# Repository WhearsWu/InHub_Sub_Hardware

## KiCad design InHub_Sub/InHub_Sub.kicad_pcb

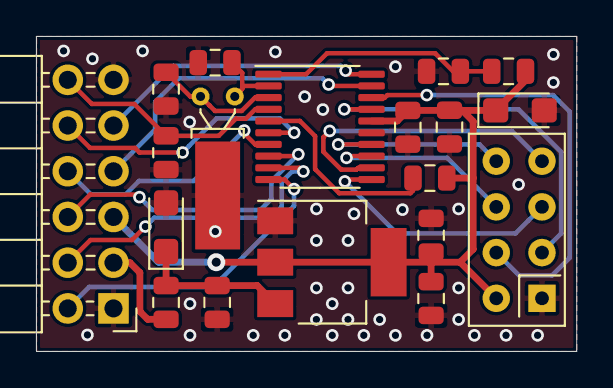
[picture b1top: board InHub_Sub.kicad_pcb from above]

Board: 2 copper layers, 30.0 x 17.5 mm, 19 parts (0 on the bottom side), 22 nets.

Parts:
C1: 0.1uF; C_0805_2012Metric
C2: 10uF_T; CP_EIA-3216-12_Kemet-S
C3: 22uF_T; CP_EIA-3216-12_Kemet-S
C4, C5: 10pF; C_0805_2012Metric
C6: 1uF; C_0805_2012Metric
C7, C10: 100nF; C_0805_2012Metric
C8: 10nF; C_0805_2012Metric
C9: 10uF; C_0805_2012Metric
F1: Fuse_Small; Fuse_0805_2012Metric
FB1: Ferrite_Bead_Small; L_0805_2012Metric
J2: Conn_02x06_Odd_Even; PinHeader_2x06_P2.54mm_Horizontal
R1, R2: 1kO; R_0805_2012Metric
U1: AMS1117-3.3; SOT-223-3_TabPin2
U2: STM32L011F4Px; TSSOP-20_4.4x6.5mm_P0.65mm
U3: NRF24L01_Breakout; nRF24L01_Breakout
Y1: 32.768kHz; Crystal_DS26_D2.0mm_L6.0mm_Horizontal_1EP_style1

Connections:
+3.3VA: FB1.2, U2.5
+3V3: C3.1, C6.1, C7.1, C9.1, C10.1, FB1.1, J2.5, R1.2, U1.2, U2.16, U3.2
+5V: F1.1, J2.3
/BOOT0: R1.1, R2.2, U2.1
/NRST: C8.1, J2.12, U2.4
/PA0: J2.10, U2.6
/PA1: J2.8, U2.7
/PA2: J2.6, U2.8
/PA3: J2.4, U2.9
/PA4: J2.2, U2.10
/SWCLK: J2.9, U2.20
/SWDIO: J2.7, U2.19
/nRF24L01_CE: U2.17, U3.3
/nRF24L01_CSN: U2.18, U3.4
/nRF24L01_IRQ: U2.14, U3.8
/nRF24L01_MISO: U2.12, U3.7
/nRF24L01_MOSI: U2.13, U3.6
/nRF24L01_SCK: U2.11, U3.5
GND: C1.2, C2.2, C3.2, C4.2, C5.2, C6.2, C7.2, C8.2, C9.2, C10.2, J2.1, J2.11, R2.1, U1.1, U2.15, U3.1, Y1.3
unnamed: C1.1, C2.1, F1.2, U1.3
unnamed: C4.1, U2.2, Y1.2
unnamed: C5.1, U2.3, Y1.1

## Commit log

2020-03-13 board layout
2020-03-15 change
2020-03-17 adjustment
